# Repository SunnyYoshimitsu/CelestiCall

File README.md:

# CelestiCall
 An attempt at making a somewhat modern smartphone with many functions. 

CelestiCall is a phone with a somewhat outdated concept that I've come up with for the Summer of 2024. The purpose of the phone? to allow me to learn and get experience on many computer subjects all at once. 
And what are those "experience" and "subjects" I'm talking about? They're power system design, FPGA design, 3D printing, communication, Linux, web design and many more.

Let me tell about what I see this phone will have as I want this to be unique and with quite a large amount of personal touch up. 
1) This phone will be running on an FPGA, specifically Zynq FPGAs. This is because I want to learn about how to create a whole SoC from scratch (with a hardcore A9 of course), as this will teach me about the SoC design and more. 
2) It will serve as both a phone and as a portable small Linux computer with HDMI. This is one reason why I said the concept is a little outdated as many modern phone can just screen share to TV and call it a day. However since my phone won't be in any of the TV's ecosystem, I will "cheat" and have it "screen-share" via HDMI. My inspiration is the ChromeBit and the Motorola Atrix HD.
3) I also will have a web "program" very much similar to what ChromeOS offer but obviously way more bootleg as it will be made by one person. This is a way that I will be able to artificially extend the power of the little device by having many computing heavy problems or storage be on the cloud. 

Here I'll go into a personal requirement for what I think the smartphone should be and have. I'll describe the software and the hardware along with the type of apps I would like to have running on it.

Requirement: 
* Interaction : All modern smartphone have touchscreens and really that's one of the reason that started the smartphone trend. I might add some physical buttons but that's up for considerations.
* 
* Communication : A phone is not a phone if one can't call from it. I'll make the phone being able to use 4G and possibly 5G as 3G and below at least in the US is defunct. Also this hopefully will allow the phone to access the internet.
* 
* Usage Time : The target is the battery lasting up to a whole day on a single charge on heavy use. I will go into what "heavy use" entails later.
* 
* Operating System : Linux is a must and also more like an existing distro. If possible and if the system is powerful enough I might use Android(possibly 2.0) since I don't have the manpower to make my own softwares.
There wil be this much requirement for now, it might be changed later.

Hardware: 
Physical dimesion: Similar to that of Iphone I or the various Window phones. 
                   Small and comact as to be able to reach from bottom of the screen to the top. 
                   
Computer Hardware: Runs off dual Cortex A9 on an FPGA and hopefully give up to 2GB of RAM. 
                   ARM A9 is a relative strong chips that could run many lightweight Linux distro without much problem. 

Software: 
Onboard-based: Android 2.0 would be preferrable
               It's a widely used distro with a lot of available softwares
               
Web-based: Something like a personal/homebrew Google Drive and the ability to use a home server as extra computing extension and a NAS as online hard-drive. 
           This would allow the device to be more than it can be

Here's the architecture of the SoC would look like: 
Note: if there's an asterisk, it means that that specific part will be custom. 

Roadmap

*Software to make calls, use WiFi, send/receive SMS, GPS and take photos in any GNU/linux:
    Estimated Time: ~5 months
    
    With hardware:
                  A7670G with ESP32: https://github.com/Xinyuan-LilyGO/LilyGO-T-A76XX
                  Quectel: https://www.aliexpress.us/item/3256806123411827.html?src=google&gatewayAdapt=glo2usa
    With software: 
                  Android 5 for Zedboard: https://github.com/noritsuna/zedroid_system_core?tab=readme-ov-file
                  Android 4 for Pynq Z2: https://xilinx-wiki.atlassian.net/wiki/spaces/A/pages/18842042/Android+4.2.2+On+Zynq+Getting+Started+Guide
                  AT commands for the GPRS 
                  Arduino C codes for ESP32 wiFi and BLE

*Touchscreen, buttons and audio I/Os:
    Estimated Time: ~2 months

    Note: as of 5/23/2024, I'm still deciding whether to pursue a phone with large or small screens. They could be as large as a modern Iphone Pro Max with screen going up to near 7inch or older phones with screen as small as 3-inch diagnally. 

    With hardware: 
                 Small 3.1 in screen: https://tailorpixels.com/product/3-1-inch-ips-tft-high-resolution-mipi/
                 Medium sized 5 in screen: https://tailorpixels.com/product/5-inch-tn-tft-lcd-rgb-800x480-landscape/
                 Large sized 7 in screen: https://tailorpixels.com/product/7-inch-tn-tft-lcd-rgb-800x480/
    With software: 
                 -For starter: a framebuffer in RAM
                 -End goal: running on a custom GPU (HyperNova)

The above two steps will be prototyped via COTS development boards and easy to use breadboard.

*Make a prototype PCB with components:

    Estimated Time: ~2 months 
    Estimated cost: ~$400

    1) Start with a simple FPGA board
    2) Add peripherals like the WiFI, GPRS and camera
    3) Add touchscreen and physical input (buttons)

 *Design and manufacture outer shell:
    Estimated Time: ~2 months
    Estimated cost: ~$50

    Design concept: The shell of the phone will be somewhat similar looking to any modern smartphone, however it will be thicker than the norm. This is to be able to accomodate at least two full size USB and HDMI ports along with possibly 2 PMODs interface. 

    With hardware: 
                 Bambu Lab 3D printer
    With software: 
                 Krita for concept art
                 Solidwork for the end product

 *End Step: 
    This step will involve the creation of the "bootleg Google Drive" that I've detailed in the beginning along with making a case for the phone.
     
Rough Project Timeline/Plans:

To do list/learn/plan(6/17):

Start making prototypes of the GPU and the Audio mixer
Then integrate them to a HDMI output

GPU: Learn about "CUDA" cores, make a RGB framebuffer of 800 x 600 size for the touchscreen output. Make variable screen resolution for HDMI out. 
Audio: extend upon school filter projects and DMA sound replay. 
       If too complicated, then make a simple PCM passthrough and FIFO for sound replay from memory. 

Integrate both GPU and Audio though the HyperNova top module to output to HDMI, display and audio jack. Add controls to allow versatile displaying. 
Possibly add possible VGA output for second display via the PMOD (max 64 colors only). 

I know this sounds ambitious as going to the moon by oneself. HOWEVER, with the way technology is evolving, I believe it's possible....Please let a student dream.....

Email: huynguyenwork123@gmail.com

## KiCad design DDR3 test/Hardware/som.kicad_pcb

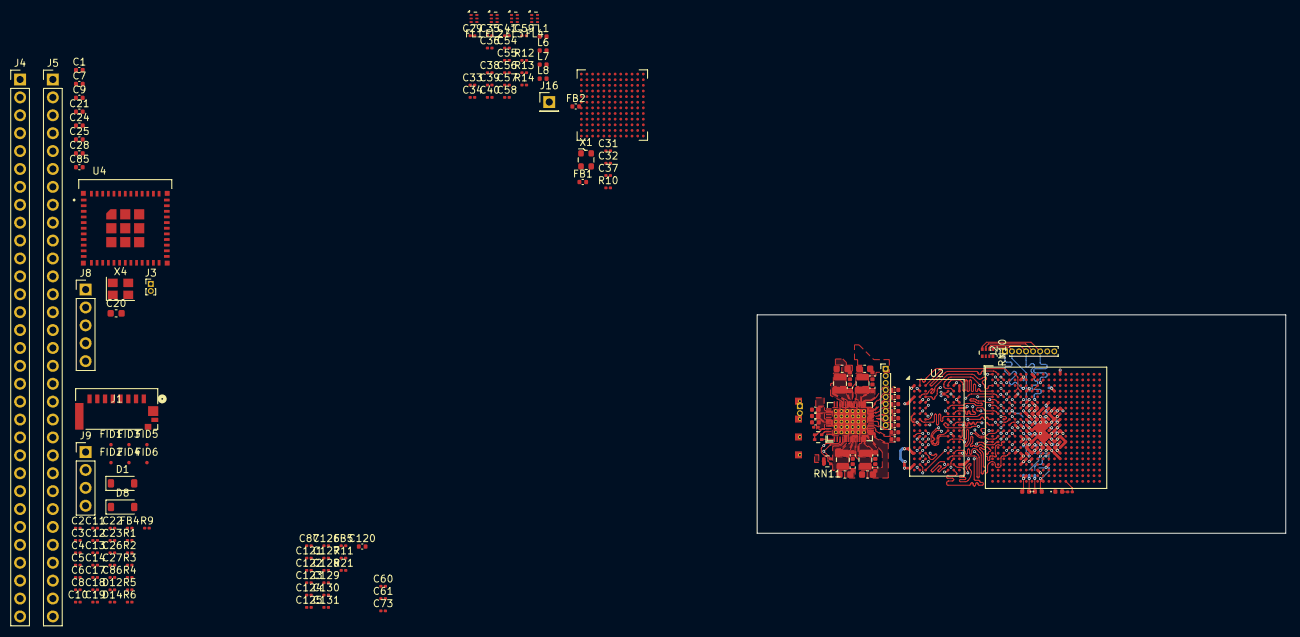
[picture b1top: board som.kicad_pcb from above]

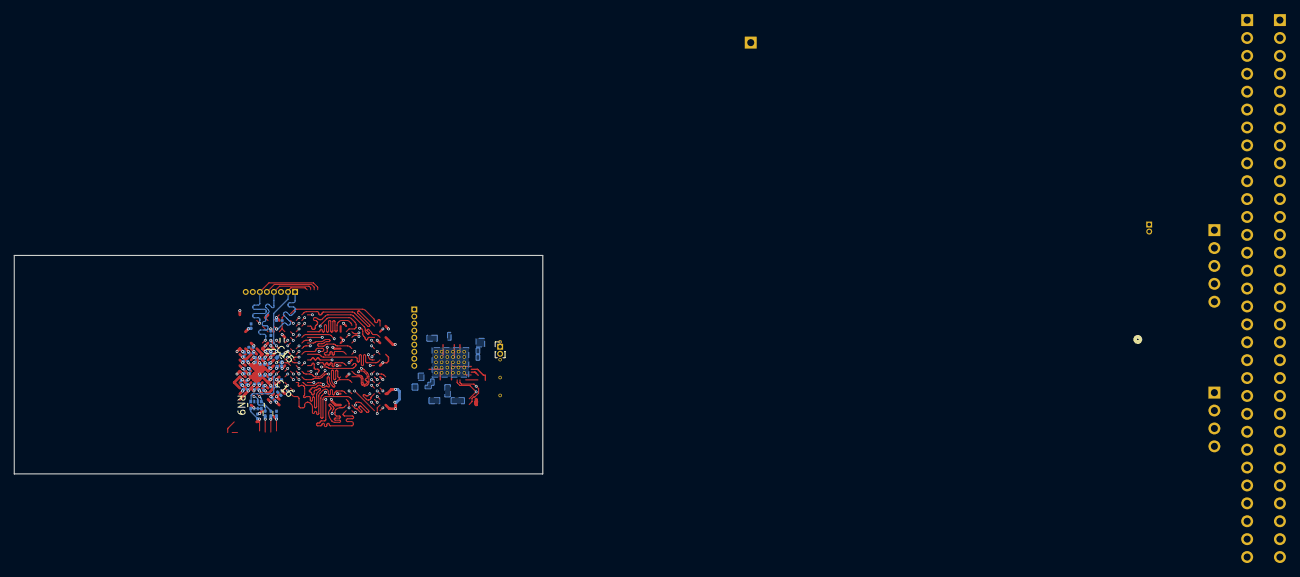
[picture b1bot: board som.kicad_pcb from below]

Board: 6 copper layers, 75.0 x 31.0 mm, 186 parts (37 on the bottom side), 206 nets.

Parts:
C1, C7, C9, C15, C24, C25, C28: 10uF; C_0402_1005Metric
C2, C3, C4, C5, C6, C8, C10, C11, C12, C13, C14, C16, C17, C18, C19, C23, C26, C27, C29, C31, C32, C33, C34, C35, C36, C38, C39, C40, C41, C54, C55, C57, C58, C59, C60, C61, C73: 0.1uF; C_0201_0603Metric
C20, C97, C100, C105, C107: 22uF; C_0603_1608Metric
C21, C85, C96, C98, C99, C101, C102, C103, C104, C106, C108, C109, C110, C111, C112, C113, C114, C115, C116, C117, C119, C120: 4u7F; C_0402_1005Metric
C22, C42, C43, C44, C45, C46, C47, C48, C49, C50, C51, C52, C62, C63, C64, C65, C66, C67, C68, C69, C70, C72, C86, C87, C88, C89, C90, C91, C92, C93, C118, C121, C122, C123, C124, C125, C126, C127, C128, C129, C130, C131: 100nF; C_0201_0603Metric
C37, C56: 18pF; C_0201_0603Metric
C53, C94: 100nF; C_0201_0603Metric_WideGap
C71: 4u7F; C_0201_0603Metric_WideGap
D1, D8: SUPK24; D_SOD-123
D2: DONE_LED; LED_0402_1005Metric
D3: INIT_LED; LED_0402_1005Metric
D7: LED3; LED_0402_1005Metric
D12, D14: TVS; R_0201_0603Metric
FB1, FB2: FerriteBead_Small; C_0402_1005Metric
FB3, FB4, FB5: 120Ω; L_0201_0603Metric
FID1, FID2, FID3, FID4, FID5, FID6: Fiducial; Fiducial_0.5mm_Mask1mm
FL1, FL2, FL3, FL4: 0850BM14E0016; Balun_Johanson_1.6x0.8mm
J1: TF; CONN12_47309-2651_MOL
J2: Conn_Debug; PinHeader_1x08_P1.00mm_Vertical
J3: Conn_MP; PinHeader_1x02_P1.00mm_Vertical
J4, J5: Conn_PB; PinHeader_1x31_P2.54mm_Vertical
J6: Conn_PWR; PinHeader_1x09_P1.00mm_Vertical
J7: Conn_IIC; PinHeader_1x02_P1.00mm_Vertical
J8: Conn_01x05_Pin; PinHeader_1x05_P2.54mm_Vertical
J9: Conn_01x04_Pin; PinHeader_1x04_P2.54mm_Vertical
J16: Conn_01x01; PinHeader_1x01_P2.54mm_Vertical
L1, L6, L7, L8: L; L_0402_1005Metric
L2, L3, L4, L5: 1uH; L_0806_2016Metric
R1, R4, R5: 80Ω; R_0201_0603Metric
R2: 4.7K; R_0201_0603Metric
R3: 4K7Ω; R_0201_0603Metric
R6: 240Ω; R_0201_0603Metric
R7, R8, R20: R; R_0201_0603Metric
R9, R21: 22Ω; R_0201_0603Metric
R10, R13: 0R; R_0201_0603Metric
R11: 40Ω; R_0201_0603Metric
R12: 14.3K; R_0201_0603Metric
R14: N/A; R_0201_0603Metric
RN9, RN10: 4K7Ω; R_Array_Convex_4x0402
RN11: 4K7Ω; R_Array_Convex_2x0402
RN12: 10KΩ; R_Array_Convex_2x0402
TP1: PMIC_PROG; TP_4pin_2.54mm
U1: XC7Z010CLG400; Xilinx_CLG400_NoPaste_JLC_Package_Delay
U2: DDR3; Micron_FBGA-96_7.5x13.5mm_Layout9x16_P0.8mm
U3: AD9361; bga-100_10_10_1p32_0p8
U4: ESP32-C6-MINI-1U-N4; XCVR_ESP32-C6-MINI-1U-N4
U7: STPMIC1; ST-WFQFN-44L_5x6mm_P0.4mm_ThermalVias
X1: SiT1602B; Oscillator_SMD_ECS_2520MV-xxx-xx-4Pin_2.5x2.0mm
X4: 33.3MHz; Crystal_SMD_3225-4Pin_3.2x2.5mm

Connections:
+1V0: C42.1, C43.1, C44.1, C45.1, C46.1, C47.1, C48.1, C49.1, C50.1, C51.1, C52.1, C53.1, C97.1, C98.1, L2.2, U1.G7 (VCCPINT[6]), U1.G11 (VCCBRAM[2]), U1.G13 (VCCINT[9]), U1.H10 (VCCBRAM[2]), U1.H12 (VCCINT[9]), U1.J7 (VCCPINT[6]), U1.J13 (VCCINT[9]), U1.K12 (VCCINT[9]), U1.L7 (VCCPINT[6]), U1.L13 (VCCINT[9]), U1.M12 (VCCINT[9]), U1.N7 (VCCPINT[6]), U1.N13 (VCCINT[9]), U1.P8 (VCCPINT[6]), U1.P12 (VCCINT[9]), U1.R7 (VCCPINT[6]), U1.R13 (VCCINT[9]), U7.5 (VOUT1)
+1V8: C29.1, C60.1, C61.1, C62.1, C63.1, C64.1, C65.1, C66.1, C67.1, C68.1, C69.1, C70.1, C73.1, C105.1, C106.1, FB3.2, J6.2, L4.2, U1.C19 (VCCO_35[6]), U1.F8 (VCCPAUX[5]), U1.F11 (VCCBATT_0), U1.F18 (VCCO_35[6]), U1.G9 (VCCPAUX[5]), U1.H8 (VCCPAUX[5]), U1.H14 (VCCO_35[6]), U1.J9 (VCCADC_0), U1.J11 (VCCAUX[6]), U1.J17 (VCCO_35[6]), U1.K8 (VCCPAUX[5]), U1.K20 (VCCO_35[6]), U1.L11 (VCCAUX[6]), U1.M8 (VCCPAUX[5]), U1.M16 (VCCO_35[6]), U1.N9 (VCCAUX[6]), U1.N11 (VCCAUX[6]), U1.P10 (VCCAUX[6]), U1.R9 (VCCAUX[6]), U7.31 (VOUT3), X1.4 (VDD)
+3.3VA: C116.1, J4.19, RN11.3 (R2.2), RN11.4 (R1.2), RN12.3 (R2.2), RN12.4 (R1.2), U7.39 (LDO4OUT), U7.42 (VIO)
+3V3: C20.1, C21.1, C22.1, C87.1, C88.1, C89.1, C90.1, C91.1, C92.1, C93.1, C94.1, C107.1, C108.1, C127.1, C128.1, C129.1, C130.1, C131.1, D2.2 (A), D3.2 (A), FB4.2, FB5.2, J1.4 (VDD), J2.8, J3.1, J5.2, J5.20, J6.1, L5.2, R3.1, RN9.1 (R1.1), RN9.2 (R2.1), RN9.3 (R3.1), RN9.4 (R4.1), RN10.5 (R4.2), RN10.6 (R3.2), RN10.7 (R2.2), RN10.8 (R1.2), U1.A6 (PS_MIO5_500), U1.A13 (VCCO_MIO1_501[4]), U1.B6 (VCCO_MIO0_500[2]), U1.B7 (PS_MIO4_500), U1.B16 (VCCO_MIO1_501[4]), U1.D7 (VCCO_MIO0_500[2]), U1.D12 (VCCO_MIO1_501[4]), U1.E15 (VCCO_MIO1_501[4]), U1.K6 (VCCO_0), U1.M6 (CFGBVS_0), U1.N6 (RSVDVCC3), U1.R6 (RSVDVCC2), U1.T6 (RSVDVCC1), U1.T8 (VCCO_13[4]), U1.U11 (VCCO_13[4]), U1.W7 (VCCO_13[4]), U1.Y10 (VCCO_13[4]), U4.3 (3V3), U7.27 (VOUT4)
+5V: C96.1, C99.1, C102.1, C104.1, C109.1, C112.1, C119.1, D1.1 (K), D8.1 (K), D12.1 (A1), D14.1 (A1), J4.9, J4.10, J6.5, J6.8, TP1.3, U7.8 (BUCK1IN), U7.12 (BUCK2IN), U7.19 (LDO25IN), U7.22 (LDO16IN), U7.24 (BUCK4IN), U7.28 (BUCK3IN), U7.36 (VIN)
/BUCK1OUT: L2.1, U7.7 (VLX1)
/BUCK2OUT: L3.1, U7.11 (VLX2)
/BUCK3OUT: L4.1, U7.29 (VLX3)
/BUCK4OUT: L5.1, U7.25 (VLX4)
/DDR_A0: U1.N2 (PS_DDR_A0_502), U2.N3 (A0)
/DDR_A1: U1.K2 (PS_DDR_A1_502), U2.P7 (A1)
/DDR_A2: U1.M3 (PS_DDR_A2_502), U2.P3 (A2)
/DDR_A3: U1.K3 (PS_DDR_A3_502), U2.N2 (A3)
/DDR_A4: U1.M4 (PS_DDR_A4_502), U2.P8 (A4)
/DDR_A5: U1.L1 (PS_DDR_A5_502), U2.P2 (A5)
/DDR_A6: U1.L4 (PS_DDR_A6_502), U2.R8 (A6)
/DDR_A7: U1.K4 (PS_DDR_A7_502), U2.R2 (A7)
/DDR_A8: U1.K1 (PS_DDR_A8_502), U2.T8 (A8)
/DDR_A9: U1.J4 (PS_DDR_A9_502), U2.R3 (A9)
/DDR_A10: U1.F5 (PS_DDR_A10_502), U2.L7 (A10/AP)
/DDR_A11: U1.G4 (PS_DDR_A11_502), U2.R7 (A11)
/DDR_A12: U1.E4 (PS_DDR_A12_502), U2.N7 (A12/~BC)
/DDR_A13: U1.D4 (PS_DDR_A13_502), U2.T3 (A13)
/DDR_A14: U1.F4 (PS_DDR_A14_502), U2.T7 (A14)
/DDR_BA0: U1.L5 (PS_DDR_BA0_502), U2.M2 (BA0)
/DDR_BA1: U1.R4 (PS_DDR_BA1_502), U2.N8 (BA1)
/DDR_BA2: U1.J5 (PS_DDR_BA2_502), U2.M3 (BA2)
/DDR_CKE: U1.N3 (PS_DDR_CKE_502), U2.K9 (CKE)
/DDR_DQ0: U1.E2 (PS_DDR_DQ8_502), U2.E3 (DQ0)
/DDR_DQ1: U1.E3 (PS_DDR_DQ9_502), U2.F7 (DQ1)
/DDR_DQ2: U1.H2 (PS_DDR_DQ13_502), U2.F2 (DQ2)
/DDR_DQ3: U1.G3 (PS_DDR_DQ10_502), U2.F8 (DQ3)
/DDR_DQ4: U1.J1 (PS_DDR_DQ15_502), U2.H3 (DQ4)
/DDR_DQ5: U1.J3 (PS_DDR_DQ12_502), U2.H8 (DQ5)
/DDR_DQ6: U1.H1 (PS_DDR_DQ14_502), U2.G2 (DQ6)
/DDR_DQ7: U1.H3 (PS_DDR_DQ11_502), U2.H7 (DQ7)
/DDR_DQ8: U1.C3 (PS_DDR_DQ0_502), U2.D7 (DQ8)
/DDR_DQ9: U1.B3 (PS_DDR_DQ1_502), U2.C3 (DQ9)
/DDR_DQ10: U1.E1 (PS_DDR_DQ7_502), U2.C8 (DQ10)
/DDR_DQ11: U1.C1 (PS_DDR_DQ6_502), U2.C2 (DQ11)
/DDR_DQ12: U1.D1 (PS_DDR_DQ5_502), U2.A7 (DQ12)
/DDR_DQ13: U1.A4 (PS_DDR_DQ3_502), U2.A2 (DQ13)
/DDR_DQ14: U1.D3 (PS_DDR_DQ4_502), U2.B8 (DQ14)
/DDR_DQ15: U1.A2 (PS_DDR_DQ2_502), U2.A3 (DQ15)
/DDR_DQM0: U1.F1 (PS_DDR_DM1_502), U2.E7 (LDM)
/DDR_DQM1: U1.A1 (PS_DDR_DM0_502), U2.D3 (UDM)
/DDR_DQS0+: U1.G2 (PS_DDR_DQS_P1_502), U2.F3 (LDQS)
/DDR_DQS0-: U1.F2 (PS_DDR_DQS_N1_502), U2.G3 (~LDQS)
/DDR_DQS1+: U1.C2 (PS_DDR_DQS_P0_502), U2.C7 (UDQS)
/DDR_DQS1-: U1.B2 (PS_DDR_DQS_N0_502), U2.B7 (~UDQS)
/DDR_ODT: U1.N5 (PS_DDR_ODT_502), U2.K1 (ODT)
/DDR_VRN: R4.1, U1.G5 (PS_DDR_VRN_502)
/DDR_VRP: R5.1, U1.H5 (PS_DDR_VRP_502)
/DDR_nCAS: U1.P5 (PS_DDR_CAS_B_502), U2.K3 (~CAS)
/DDR_nCS: U1.N1 (PS_DDR_CS_B_502), U2.L2 (~CS)
/DDR_nRAS: U1.P4 (PS_DDR_RAS_B_502), U2.J3 (~RAS)
/DDR_nWE: U1.M5 (PS_DDR_WE_B_502), U2.L3 (~WE)
/DONE_: D2.1 (K), R7.2
/EXT_SYNC: J16.1, R14.1
/INIT_: D3.1 (K), R8.2
/LED3_: D7.2 (A), R20.2
/PMIC_INTLDO: C117.1, C118.1, U7.40 (INTLDO)
/PS_CLK_: R9.1, X4.3 (OUT)
/SD0_CK_: R11.1, U1.D14 (PS_MIO40_501)
/TRANS_CMOS_FB_CLK: U1.K18 (IO_L12N_T1_MRCC_35), U3.F10 (FB_CLK+)
/TRANS_CMOS_RX_D0: U1.E17 (IO_L3P_T0_DQS_AD1P_35), U3.K11 (P1_D0/RX_D0-)
/TRANS_CMOS_RX_D1: U1.F16 (IO_L6P_T0_35), U3.J12 (P1_D1/RX_D0+)
/TRANS_CMOS_RX_D2: U1.J20 (IO_L17P_T2_AD5P_35), U3.K10 (P1_D2/RX_D1-)
/TRANS_CMOS_RX_D3: U1.F17 (IO_L6N_T0_VREF_35), U3.J11 (P1_D3/RX_D1+)
/TRANS_CMOS_RX_D4: U1.F20 (IO_L15N_T2_DQS_AD12N_35), U3.K9 (P1_D4/RX_D2-)
/TRANS_CMOS_RX_D5: U1.G15 (IO_L19N_T3_VREF_35), U3.J10 (P1_D5/RX_D2+)
/TRANS_CMOS_RX_D6: U1.G19 (IO_L18P_T2_AD13P_35), U3.K8 (P1_D6/RX_D3-)
/TRANS_CMOS_RX_D7: U1.G17 (IO_L16P_T2_35), U3.J9 (P1_D7/RX_D3+)
/TRANS_CMOS_RX_D8: U1.E18 (IO_L5P_T0_AD9P_35), U3.K7 (P1_D8/RX_D4-)
/TRANS_CMOS_RX_D9: U1.G18 (IO_L16N_T2_35), U3.J8 (P1_D9/RX_D4+)
/TRANS_CMOS_RX_D10: U1.E19 (IO_L5N_T0_AD9N_35), U3.J7 (P1_D10/RX_D5-)
/TRANS_CMOS_RX_D11: U1.H18 (IO_L14N_T2_AD4N_SRCC_35), U3.H8 (P1_D11/RX_D5+)
/TRANS_CMOS_RX_FRAME: U1.H17 (IO_L13N_T2_MRCC_35), U3.G8 (RX_FRAME+)
/TRANS_CMOS_TX_D0: U1.M18 (IO_L8N_T1_AD10N_35), U3.E12 (P0_D0/TX_D0-)
/TRANS_CMOS_TX_D1: U1.L17 (IO_L11N_T1_SRCC_35), U3.D11 (P0_D1/TX_D0+)
/TRANS_CMOS_TX_D2: U1.M19 (IO_L7P_T1_AD2P_35), U3.E11 (P0_D2/TX_D1-)
/TRANS_CMOS_TX_D3: U1.M15 (IO_L23N_T3_35), U3.D10 (P0_D3/TX_D1+)
/TRANS_CMOS_TX_D4: U1.K16 (IO_L24P_T3_AD15P_35), U3.E10 (P0_D4/TX_D2-)
/TRANS_CMOS_TX_D5: U1.M17 (IO_L8P_T1_AD10P_35), U3.D9 (P0_D5/TX_D2+)
/TRANS_CMOS_TX_D6: U1.J16 (IO_L24N_T3_AD15N_35), U3.E9 (P0_D6/TX_D3-)
/TRANS_CMOS_TX_D7: U1.N16 (IO_L21N_T3_DQS_AD14N_35), U3.D8 (P0_D7/TX_D3+)
/TRANS_CMOS_TX_D8: U1.L16 (IO_L11P_T1_SRCC_35), U3.E8 (P0_D8/TX_D4-)
/TRANS_CMOS_TX_D9: U1.M14 (IO_L23P_T3_35), U3.D7 (P0_D9/TX_D4+)
/TRANS_CMOS_TX_D10: U1.H15 (IO_L19P_T3_35), U3.F8 (P0_D10/TX_D5-)
/TRANS_CMOS_TX_D11: U1.K19 (IO_L10P_T1_AD11P_35), U3.E7 (P0_D11/TX_D5+)
/TRANS_CMOS_TX_FRAME: U1.J19 (IO_L10N_T1_AD11N_35), U3.G9 (TX_FRAME+)
/TRANS_CTRL_IN0: U1.L14 (IO_L22P_T3_AD7P_35), U3.C5 (CTRL_IN0)
/TRANS_CTRL_IN1: U1.L15 (IO_L22N_T3_AD7N_35), U3.C6 (CTRL_IN1)
/TRANS_CTRL_IN2: U1.J15 (IO_25_35), U3.D6 (CTRL_IN2)
/TRANS_CTRL_IN3: U1.K14 (IO_L20P_T3_AD6P_35), U3.D5 (CTRL_IN3)
/TRANS_CTRL_OUT0: U1.B20 (IO_L1N_T0_AD0N_35), U3.D4 (CTRL_OUT0)
/TRANS_CTRL_OUT1: U1.A20 (IO_L2N_T0_AD8N_35), U3.E4 (CTRL_OUT1)
/TRANS_CTRL_OUT2: U1.J14 (IO_L20N_T3_AD6N_35), U3.E5 (CTRL_OUT2)
/TRANS_CTRL_OUT3: U1.C20 (IO_L1P_T0_AD0P_35), U3.E6 (CTRL_OUT3)
/TRANS_CTRL_OUT4: U1.G20 (IO_L18N_T2_AD13N_35), U3.F6 (CTRL_OUT4)
/TRANS_CTRL_OUT5: U1.N15 (IO_L21P_T3_DQS_AD14P_35), U3.F5 (CTRL_OUT5)
/TRANS_CTRL_OUT6: U1.L20 (IO_L9N_T1_DQS_AD3N_35), U3.F4 (CTRL_OUT6)
/TRANS_CTRL_OUT7: U1.D19 (IO_L4P_T0_35), U3.G4 (CTRL_OUT7)
/TRANS_ENABLE: U1.D18 (IO_L3N_T0_DQS_AD1N_35), U3.G6 (ENABLE)
/TRANS_ENAGC: U1.J18 (IO_L14P_T2_AD4P_SRCC_35), U3.G5 (EN_AGC)
/TRANS_MRCC_CLKOUT: U1.H16 (IO_L13P_T2_MRCC_35), U3.J6 (CLK_OUT)
/TRANS_MRCC_DATA_CLK: U1.K17 (IO_L12P_T1_MRCC_35), U3.G11 (DATA_CLK+)
/TRANS_OSC_N: C37.1, X1.3 (OUT)
/TRANS_RBIAS: R12.1, U3.L4 (RBIAS)
/TRANS_RST: U1.B14 (PS_MIO47_501), U3.K5 (~RESET)
/TRANS_RXRF0_N: C39.1, FL3.3 (RF_N)
/TRANS_RXRF0_P: C38.1, FL3.4 (RF_P)
/TRANS_RXRF1_N: C54.1, FL4.3 (RF_N)
/TRANS_RXRF1_P: C41.1, FL4.4 (RF_P)
/TRANS_SPI_CLK: U1.A16 (PS_MIO24_501), U3.J5 (SPI_CLK)
/TRANS_SPI_MISO: U1.D11 (PS_MIO23_501), U3.L6 (SPI_MISO)
/TRANS_SPI_MOSI: U1.B17 (PS_MIO22_501), U3.J4 (SPI_MOSI)
/TRANS_SPI_SS: U1.F15 (PS_MIO25_501), U3.K6 (SPI_~EN)
/TRANS_SYNC: R13.1, U1.H20 (IO_L17N_T2_AD5N_35)
/TRANS_TXNRX: U1.D20 (IO_L4N_T0_35), U3.H4 (TX~RX)
/TRANS_TXRF0_N: C33.1, FL1.4 (RF_P)
/TRANS_TXRF0_P: C34.1, FL1.3 (RF_N)
/TRANS_TXRF1_N: C36.1, FL2.4 (RF_P)
/TRANS_TXRF1_P: C35.1, FL2.3 (RF_N)
/VCC_PLL: C71.1, C72.1, FB3.1, U1.G8 (VCCPLL)
/VCC_PL_CLK: C120.1, C121.1, FB5.1
/VCC_PS_CLK: C85.1, C86.1, FB4.1, X4.1 (EN), X4.4 (Vdd)
/VREF_DDR1: C18.1, C23.1, C24.1, U1.H6 (PS_DDR_VREF0_502), U1.P6 (PS_DDR_VREF1_502)
/VREF_DDR2: C26.1, U2.M8 (VREFCA)
/VREF_DDR3: C28.1, U2.H1 (VREFDQ)
DDR_CK+: R1.1, U1.L2 (PS_DDR_CKP_502), U2.J7 (CK)
DDR_CK-: R1.2, U1.M2 (PS_DDR_CKN_502), U2.K7 (~CK)
DDR_nRST: R2.1, U1.B4 (PS_DDR_DRST_B_502), U2.T2 (~RESET)
DONE: R7.1, RN9.6 (R3.2), U1.R11 (DONE_0)
GND: C1.2, C2.2, C3.2, C4.2, C5.2, C6.2, C7.2, C8.2, C9.2, C10.2, C11.2, C12.2, C13.2, C14.2, C15.2, C16.2, C17.2, C18.2, C19.2, C20.2, C21.2, C22.2, C23.2, C24.2, C25.2, C26.2, C27.2, C28.2, C29.2, C31.1, C32.1, C42.2, C43.2, C44.2, C45.2, C46.2, C47.2, C48.2, C49.2, C50.2, C51.2, C52.2, C53.2, C56.1, C57.1, C58.1, C59.1, C60.2, C61.2, C62.2, C63.2, C64.2, C65.2, C66.2, C67.2, C68.2, C69.2, C70.2, C71.2, C72.2, C73.2, C85.2, C86.2, C87.2, C88.2, C89.2, C90.2, C91.2, C92.2, C93.2, C94.2, C96.2, C97.2, C98.2, C99.2, C100.2, C101.2, C102.2, C103.2, C104.2, C105.2, C106.2, C107.2, C108.2, C109.2, C110.2, C111.2, C112.2, C113.2, C114.2, C115.2, C116.2, C117.2, C118.2, C119.2, C120.2, C121.2, C122.2, C123.2, C124.2, C125.2, C126.2, C127.2, C128.2, C129.2, C130.2, C131.2, D7.1 (K), D12.2 (A2), D14.2 (A2), FL1.5 (GND), FL1.6 (GND), FL2.5 (GND), FL2.6 (GND), FL3.5 (GND), FL3.6 (GND), FL4.5 (GND), FL4.6 (GND), J1.6 (VSS), J1.G1, J1.G2, J1.G3, J1.G4, J2.7, J3.2, J4.11, J4.12, J4.27, J4.30, J4.31, J5.18, J5.19, J6.3, J9.4, R2.2, R5.2, R6.1, R12.2, TP1.4, U1.A5 (PS_MIO6_500), U1.A8 (GND[59]), U1.A18 (GND[59]), U1.B1 (GND[59]), U1.B8 (PS_MIO2_500), U1.B11 (GND[59]), U1.C4 (GND[59]), U1.C9 (GND[59]), U1.C14 (GND[59]), U1.D5 (PS_MIO8_500), U1.D6 (PS_MIO3_500), U1.D8 (PS_MIO7_500), U1.D17 (GND[59]), U1.E10 (GND[59]), U1.E20 (GND[59]), U1.F3 (GND[59]), U1.F7 (GND[59]), U1.G10 (GND[59]), U1.G12 (GND[59]), U1.G16 (GND[59]), U1.H7 (GND[59]), U1.H9 (GND[59]), U1.H11 (GND[59]), U1.H13 (GND[59]), U1.H19 (GND[59]), U1.J2 (GND[59]), U1.J8 (GND[59]), U1.J10 (GNDADC_0), U1.J12 (GND[59]), U1.K5 (GND[59]), U1.K7 (GND[59]), U1.K9 (VP_0), U1.K10 (VREFN_0), U1.K11 (GND[59]), U1.K13 (GND[59]), U1.K15 (GND[59]), U1.L8 (GND[59]), U1.L9 (VREFP_0), U1.L10 (VN_0), U1.L12 (GND[59]), U1.L18 (GND[59]), U1.M1 (GND[59]), U1.M7 (GND[59]), U1.M9 (DXP_0), U1.M10 (DXN_0), U1.M11 (GND[59]), U1.M13 (GND[59]), U1.N4 (GND[59]), U1.N8 (GND[59]), U1.N10 (GND[59]), U1.N12 (GND[59]), U1.N14 (GND[59]), U1.P7 (GND[59]), U1.P9 (GND[59]), U1.P11 (GND[59]), U1.P13 (GND[59]), U1.P17 (GND[59]), U1.R8 (GND[59]), U1.R12 (GND[59]), U1.R20 (GND[59]), U1.T3 (GND[59]), U1.T7 (GND[59]), U1.T13 (GND[59]), U1.U6 (GND[59]), U1.U16 (GND[59]), U1.V9 (GND[59]), U1.V19 (GND[59]), U1.W2 (GND[59]), U1.W12 (GND[59]), U1.Y5 (GND[59]), U1.Y15 (GND[59]), U2.A9 (VSS), U2.B1 (VSSQ), U2.B3 (VSS), U2.B9 (VSSQ), U2.D1 (VSSQ), U2.D8 (VSSQ), U2.E1 (VSS), U2.E2 (VSSQ), U2.E8 (VSSQ), U2.F9 (VSSQ), U2.G1 (VSSQ), U2.G8 (VSS), U2.G9 (VSSQ), U2.J2 (VSS), U2.J8 (VSS), U2.M1 (VSS), U2.M9 (VSS), U2.P1 (VSS), U2.P9 (VSS), U2.T1 (VSS), U2.T9 (VSS), U3.C1 (RX2C-), U3.D1 (RX2C+), U3.E1 (RX2B+), U3.F1 (RX2B-), U3.G7 (RX_FRAME-), U3.G10 (FB_CLK-), U3.H1 (RX1B+), U3.H9 (TX_FRAME-), U3.J1 (RX1B-), U3.K1 (RX1C+), U3.L1 (RX1C-), U4.1 (GND1), U4.2 (GND1__1), U4.11 (GND1__2), U4.14 (GND1__3), U4.36 (GND1__4), U4.37 (GND1__5), U4.38 (GND1__6), U4.39 (GND1__7), U4.40 (GND1__8), U4.41 (GND1__9), U4.42 (GND1__10), U4.43 (GND1__11), U4.44 (GND1__12), U4.45 (GND1__13), U4.46 (GND1__14), U4.47 (GND2), U4.48 (GND2__1), U4.49_1 (GND2__2), U4.49_2 (GND2__3), U4.49_3 (GND2__4), U4.49_4 (GND2__5), U4.49_5 (GND2__6), U4.49_6 (GND2__7), U4.49_7 (GND2__8), U4.49_8 (GND2__9), U4.49_9 (GND2__10), U4.50 (GND2__11), U4.51 (GND2__12), U4.52 (GND2__13), U4.53 (GND2__14), U7.6 (PGND1), U7.10 (PGND2), U7.15 (GNDLDO), U7.26 (PGND4)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
INIT: R8.1, RN9.5 (R4.2), U1.R10 (INIT_B_0)
JTAG_TCK: J2.4, RN10.2 (R2.1), U1.F9 (TCK_0), U4.9 (IO4)
JTAG_TDI: J2.2, RN10.1 (R1.1), U1.G6 (TDI_0), U4.5 (IO2)
JTAG_TDO: J2.3, U1.F6 (TDO_0), U4.6 (IO3)
JTAG_TMS: J2.5, RN10.3 (R3.1), U1.J6 (TMS_0), U4.10 (IO5)
LDO2: C113.1, J6.9, U7.18 (LDO2OUT)
LDO5: C114.1, J6.7, U7.20 (LDO5OUT)
LDO6: C111.1, J6.6, U7.21 (LDO6OUT)
LED3: R20.1, U1.Y14 (IO_L8N_T1_34)
MB_SCL: J7.2, RN11.2 (R2.1), TP1.2, U7.4 (SCL)
MB_SDA: J7.1, RN11.1 (R1.1), TP1.1, U7.3 (SDA)
N20+: J4.1, U1.N20 (IO_L14P_T2_SRCC_34)
unnamed: D1.2 (A), J5.1
unnamed: D8.2 (A), J8.5
unnamed: R6.2, U2.L8 (ZQ)
unnamed: C38.2, U3.M1 (RX1A+)
unnamed: C39.2, U3.M2 (RX1A-)
unnamed: C41.2, U3.A2 (RX2A+)
unnamed: C54.2, U3.A1 (RX2A-)
unnamed: C55.2, U3.G1 (RX_EXT_LO_IN)
unnamed: R13.2, R14.2, U3.H5 (SYNC_IN)
unnamed: C34.2, L1.2, U3.M7 (TX1A+)
unnamed: C33.2, L6.2, U3.M8 (TX1A-)
unnamed: C31.2, C32.2, FB1.2, L1.1, L6.1, U3.M9 (TX1B+), U3.M10 (TX1B-)
unnamed: C35.2, L7.2, U3.A8 (TX2A+)
unnamed: C36.2, L8.2, U3.A7 (TX2A-)
unnamed: C57.2, C58.2, C59.2, FB2.2, L7.1, L8.1, U3.A9 (TX2B-), U3.A10 (TX2B+)
unnamed: C40.2, U3.A12 (TX_EXT_LO_IN)
unnamed: C37.2, C56.2, U3.M12 (XTALN)
unnamed: R3.2, U4.8 (EN)
unnamed: R10.1, X1.1 (Tri-State)
P20-: J4.2, U1.P19 (IO_L13N_T2_MRCC_34)
PL_CLK: R21.2, U1.V13 (IO_L3N_T0_DQS_34)
PMIC_INT: RN12.2 (R2.1), U7.43 (INTn)
PMIC_PON: J5.17, U7.17 (PONKEYn)
PMIC_nRST: J2.1, RN12.1 (R1.1), U1.C7 (PS_POR_B_500), U7.1 (RSTn)
PROGRAM: RN9.8 (R1.2), U1.L6 (PROGRAM_B_0)
PS_CLK: R9.2, U1.E7 (PS_CLK_500)
PS_SRST: J2.6, RN10.4 (R4.1), U1.B10 (PS_SRST_B_501)
SD0_CK: J1.5 (CLK), R11.2
SD0_CMD: J1.3 (CMD), U1.C17 (PS_MIO41_501)
SD0_D0: J1.7 (DAT0), U1.E12 (PS_MIO42_501)
SD0_D1: J1.8 (DAT1), U1.A9 (PS_MIO43_501)
SD0_D2: J1.1 (DAT2), U1.F13 (PS_MIO44_501)
SD0_D3: J1.2 (DAT3/CD), U1.B15 (PS_MIO45_501)
T20+: J4.3, U1.P20 (IO_L14N_T2_SRCC_34)
TTY_MISO: J8.4, U4.30 (RXD0)
TTY_MOSI: J8.3, U4.31 (TXD0)
U18+: J4.21, U1.U18 (IO_L12P_T1_MRCC_34)
U20-: J4.4, U1.T20 (IO_L15P_T2_DQS_34)
USB_D+: J9.2, U4.18 (IO13)
USB_D-: J9.1, U4.17 (IO12)
V15+: J4.25, U1.V15 (IO_L10P_T1_34)
V16+: J4.23, U1.V16 (IO_L18P_T2_34)
V18: J4.20, U1.V18 (IO_L21N_T3_DQS_34)
V20+: J4.5, U1.T19 (IO_25_34)
VCC_DDR: C1.1, C2.1, C3.1, C4.1, C5.1, C6.1, C7.1, C8.1, C9.1, C10.1, C11.1, C12.1, C13.1, C14.1, C15.1, C16.1, C17.1, C19.1, C25.1, C27.1, C100.1, C101.1, L3.2, R4.2, U1.A3 (VCCO_DDR_502[10]), U1.D2 (VCCO_DDR_502[10]), U1.E5 (VCCO_DDR_502[10]), U1.G1 (VCCO_DDR_502[10]), U1.H4 (VCCO_DDR_502[10]), U1.L3 (VCCO_DDR_502[10]), U1.P2 (VCCO_DDR_502[10]), U1.R5 (VCCO_DDR_502[10]), U1.U1 (VCCO_DDR_502[10]), U1.V4 (VCCO_DDR_502[10]), U2.A1 (VDDQ), U2.A8 (VDDQ), U2.B2 (VDD), U2.C1 (VDDQ), U2.C9 (VDDQ), U2.D2 (VDDQ), U2.D9 (VDD), U2.E9 (VDDQ), U2.F1 (VDDQ), U2.G7 (VDD), U2.H2 (VDDQ), U2.H9 (VDDQ), U2.K2 (VDD), U2.K8 (VDD), U2.N1 (VDD), U2.N9 (VDD), U2.R1 (VDD), U2.R9 (VDD), U7.9 (VOUT2), U7.13 (LDO3IN)
VDD: C110.1, C122.1, C123.1, C124.1, C125.1, C126.1, J6.4, U1.N19 (VCCO_34[6]), U1.R15 (VCCO_34[6]), U1.T18 (VCCO_34[6]), U1.V14 (VCCO_34[6]), U1.W17 (VCCO_34[6]), U1.Y20 (VCCO_34[6]), U7.23 (LDO1OUT)
VREF_DDR: C103.1, U7.16 (VREFDDR)
VTT_DDR: C115.1, U7.14 (LDO3OUT)
W15-: J4.24, U1.W15 (IO_L10N_T1_34)
W16-: J4.22, U1.W16 (IO_L18N_T2_34)
W18+: J4.16, U1.W18 (IO_L22P_T3_34)
W19-: J4.14, U1.W19 (IO_L22N_T3_34)
W20-: J4.6, U1.U20 (IO_L15N_T2_DQS_34)
Y16: J4.18, U1.Y16 (IO_L7P_T1_34)
Y16+: J4.7, U1.U19 (IO_L12N_T1_MRCC_34)
Y17: J4.17, U1.Y17 (IO_L7N_T1_34)
Y17-: J4.8, U1.V20 (IO_L16P_T2_34)
Y18+: J4.15, U1.Y18 (IO_L17P_T2_34)
Y19-: J4.13, U1.Y19 (IO_L17N_T2_34)

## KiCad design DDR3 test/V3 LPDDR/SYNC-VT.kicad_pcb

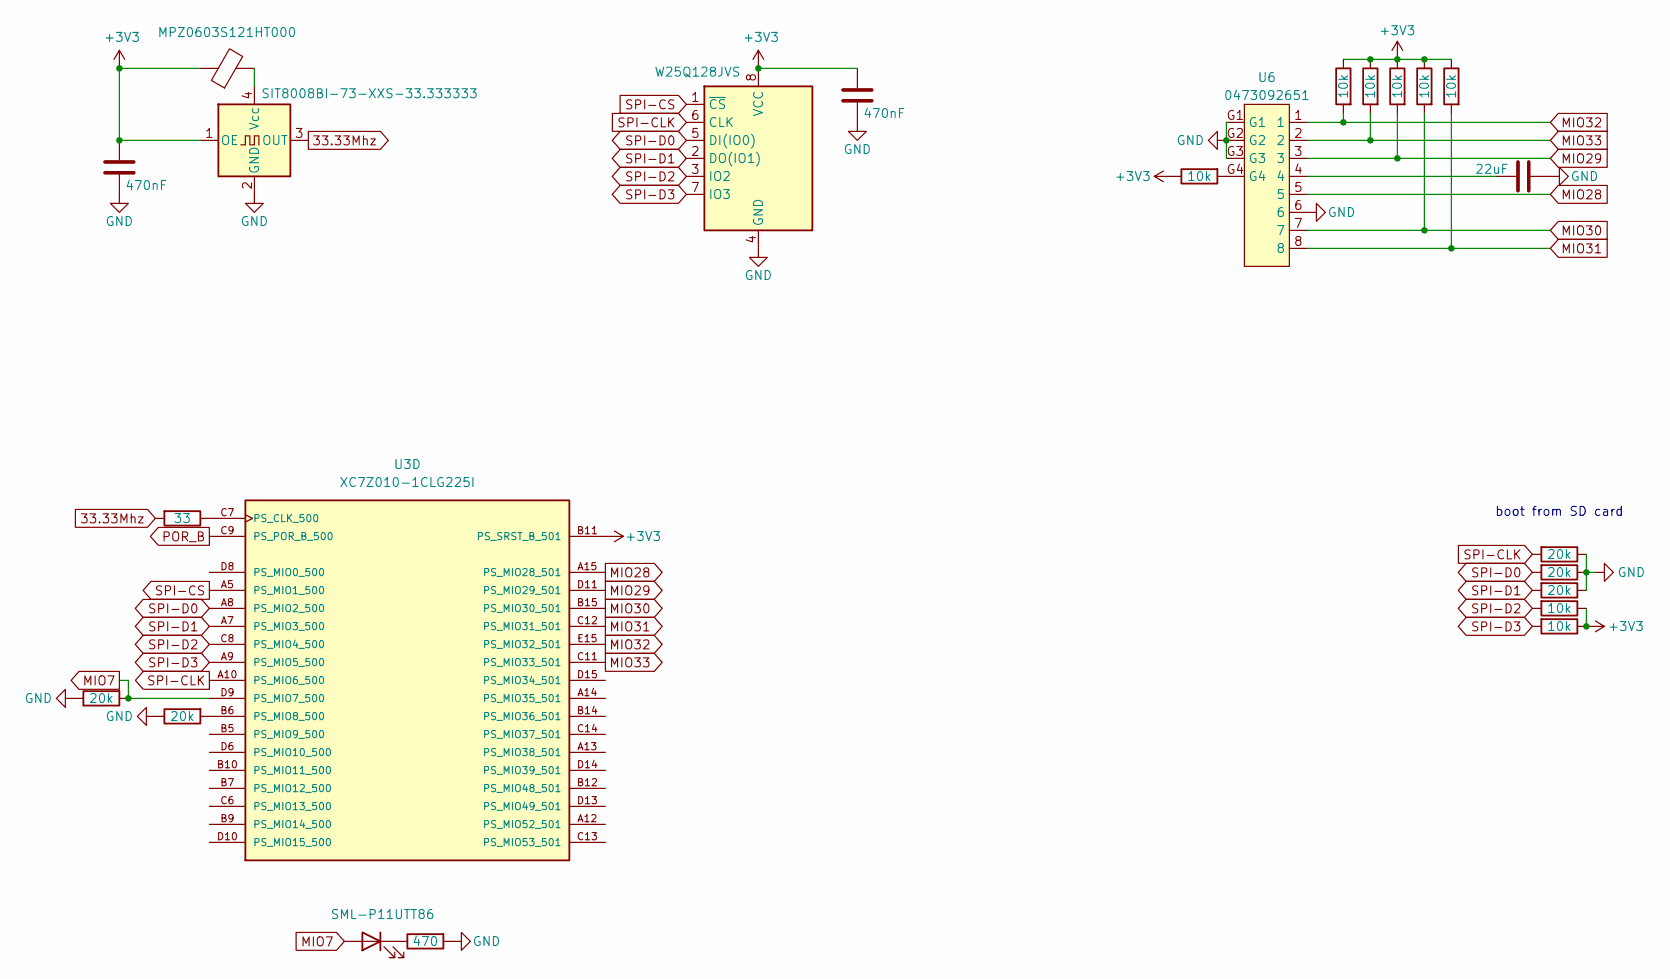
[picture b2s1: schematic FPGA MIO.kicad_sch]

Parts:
C1: 22uF; C_0402_1005Metric
C26, C27: 470nF; C_0201_0603Metric
D2: SML-P11UTT86; LED_0402_1005Metric
FB3: MPZ0603S121HT000; C_0201_0603Metric
R14, R15, R16, R17, R20: 20k; R_0201_0603Metric
R18, R19, R23, R24, R25, R26, R27, R28: 10k; R_0402_1005Metric
R21: 33; R_0201_0603Metric
R22: 470; R_0201_0603Metric
U3: XC7Z010-1CLG225I; BGA225C80P15X15_1300X1300X150N; MPN XC7Z010-1CLG225I
U5: W25Q128JVS; SOIC-8_5.23x5.23mm_P1.27mm
U6: 0473092651; CONN12_47309-2651_MOL
X1: SIT8008BI-73-XXS-33.333333; Oscillator_SMD_SeikoEpson_SG210-4Pin_2.5x2.0mm

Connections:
33.33Mhz: R21.2, X1.3 (OUT)
+3V3: C26.1, C27.1, FB3.1, R18.1, R19.1, R23.1, R24.1, R25.1, R26.1, R27.1, R28.1, U3.B11 (PS_SRST_B_501), U5.8 (VCC), X1.1 (OE); also elsewhere on the board
GND: C1.2, C26.2, C27.2, R14.1, R15.1, R16.1, R17.1, R20.1, R22.2, U5.4 (GND), U6.6, U6.G1, U6.G2, U6.G3, X1.2 (GND); also elsewhere on the board
MIO7: D2.2 (A), R20.2, U3.D9 (PS_MIO7_500)
MIO28: U3.A15 (PS_MIO28_501), U6.5
MIO29: R26.2, U3.D11 (PS_MIO29_501), U6.3
MIO30: R27.2, U3.B15 (PS_MIO30_501), U6.7
MIO31: R28.2, U3.C12 (PS_MIO31_501), U6.8
MIO32: R24.2, U3.E15 (PS_MIO32_501), U6.1
MIO33: R25.2, U3.C11 (PS_MIO33_501), U6.2
unnamed: C1.1, U6.4
unnamed: D2.1 (K), R22.1
unnamed: R23.2, U6.G4
unnamed: R21.1, U3.C7 (PS_CLK_500)
unnamed: R14.2, U3.B6 (PS_MIO8_500)
unnamed: FB3.2, X1.4 (Vcc)
POR_B: U3.C9 (PS_POR_B_500); also elsewhere on the board
SPI-CLK: R15.2, U3.A10 (PS_MIO6_500), U5.6 (CLK)
SPI-CS: U3.A5 (PS_MIO1_500), U5.1 (~CS)
SPI-D0: R16.2, U3.A8 (PS_MIO2_500), U5.5 (DI(IO0))
SPI-D1: R17.2, U3.A7 (PS_MIO3_500), U5.2 (DO(IO1))
SPI-D2: R18.2, U3.C8 (PS_MIO4_500), U5.3 (IO2)
SPI-D3: R19.2, U3.A9 (PS_MIO5_500), U5.7 (IO3)

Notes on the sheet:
boot from SD card

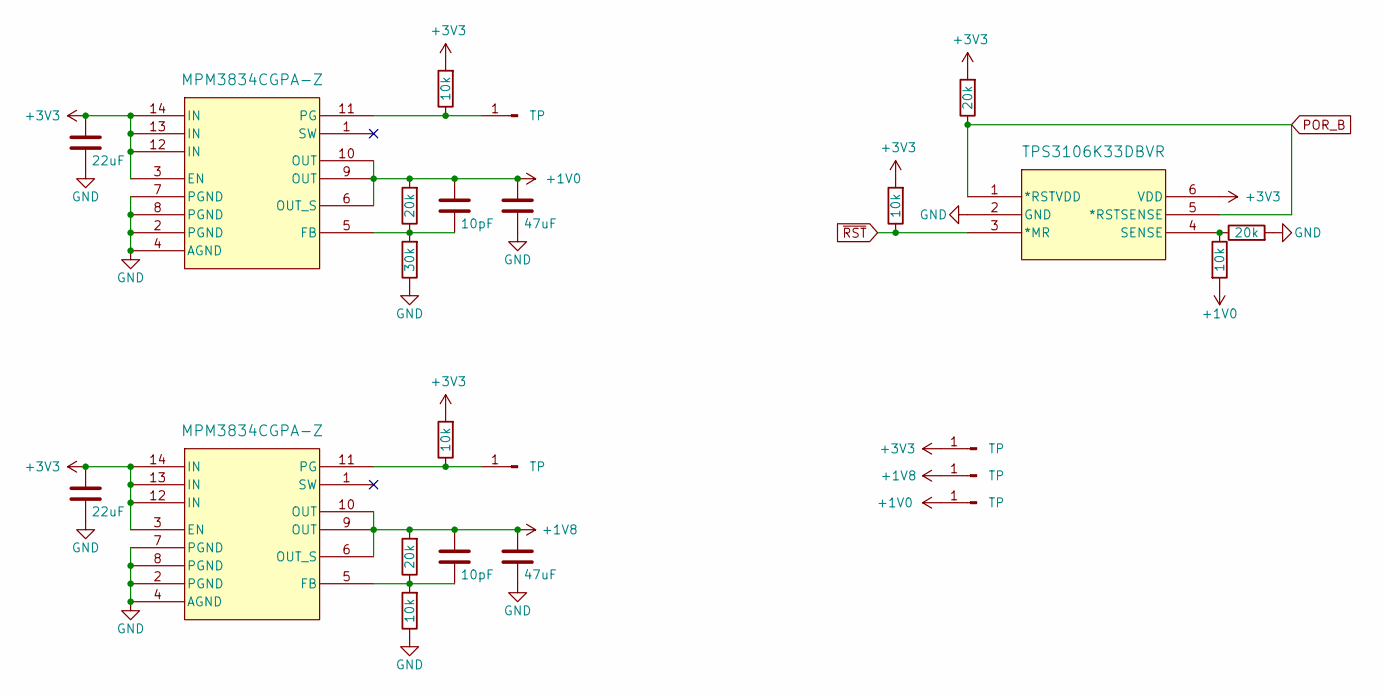
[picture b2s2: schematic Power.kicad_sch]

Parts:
C5, C11: 10pF; C_0201_0603Metric
C8, C10: 22uF; C_0402_1005Metric
C9, C12: 47uF; C_0805_2012Metric
R1, R3, R8, R10: 20k; C_0201_0603Metric
R2: 30k; C_0402_1005Metric
R4, R5, R6, R7, R9: 10k; C_0402_1005Metric
TP1, TP2, TP3, TP4, TP5: TP; TestPoint_Pad_1.0x1.0mm
U1, U2: MPM3834CGPA-Z; ECLGA-14_MPM3834C_MNP
U4: TPS3106K33DBVR; DBV6-L

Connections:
+1V0: C5.1, C9.1, R1.2, R9.2, TP5.1, U1.6 (OUT_S), U1.9 (OUT), U1.10 (OUT); also elsewhere on the board
+1V8: C11.1, C12.1, R3.2, TP4.1, U2.6 (OUT_S), U2.9 (OUT), U2.10 (OUT); also elsewhere on the board
+3V3: C8.1, C10.1, R4.2, R6.2, R7.2, R10.2, TP3.1, U1.3 (EN), U1.12 (IN), U1.13 (IN), U1.14 (IN), U2.3 (EN), U2.12 (IN), U2.13 (IN), U2.14 (IN), U4.6 (VDD); also elsewhere on the board
GND: C8.2, C9.2, C10.2, C12.2, R2.1, R5.1, R8.2, U1.2 (PGND), U1.4 (AGND), U1.7 (PGND), U1.8 (PGND), U2.2 (PGND), U2.4 (AGND), U2.7 (PGND), U2.8 (PGND), U4.2 (GND); also elsewhere on the board
unnamed: R6.1, TP1.1, U2.11 (PG)
unnamed: R4.1, TP2.1, U1.11 (PG)
unnamed: C5.2, R1.1, R2.2, U1.5 (FB)
unnamed: C11.2, R3.1, R5.2, U2.5 (FB)
unnamed: R8.1, R9.1, U4.4 (SENSE)
POR_B: R10.1, U4.1 (*RSTVDD), U4.5 (*RSTSENSE); also elsewhere on the board
~RST: R7.1, U4.3 (*MR)

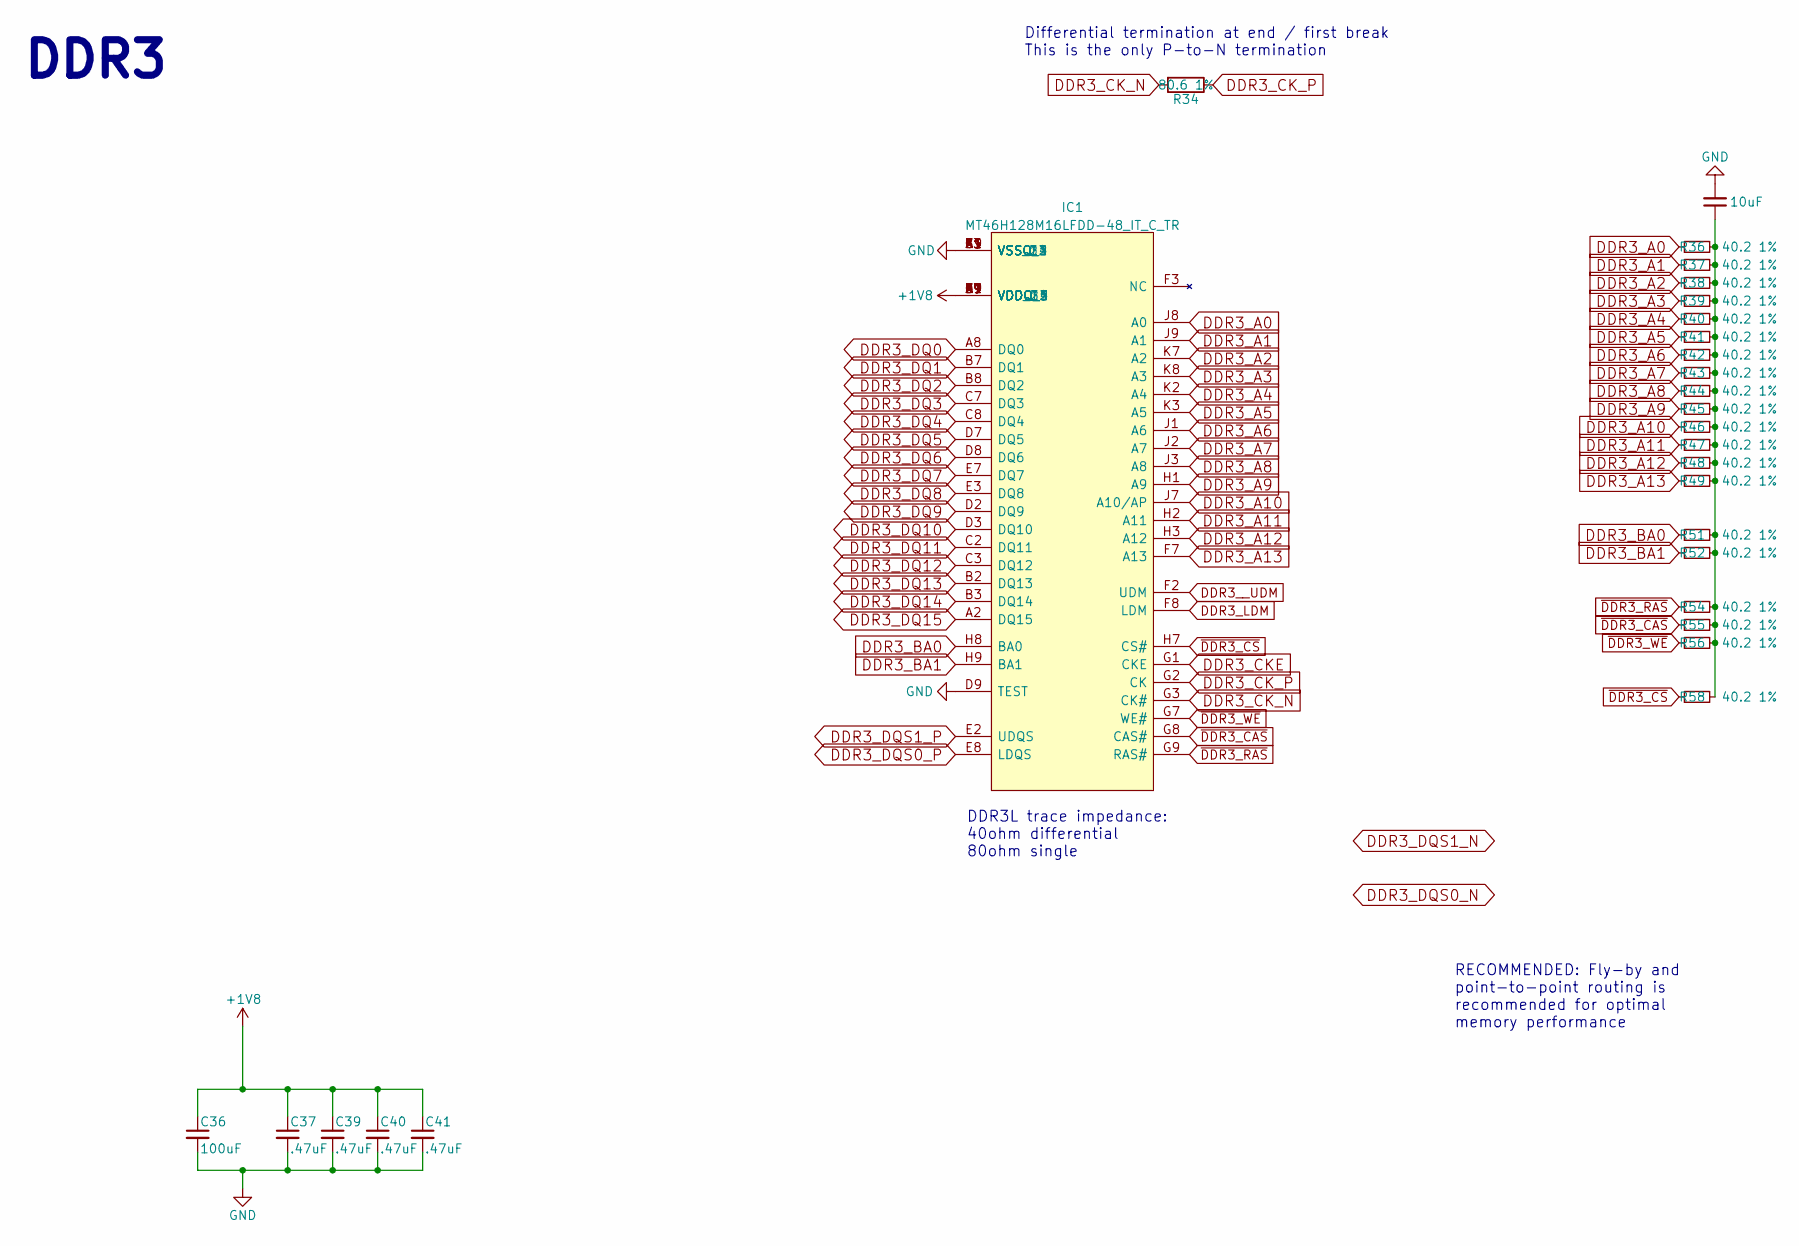
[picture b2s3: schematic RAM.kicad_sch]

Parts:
C36: 100uF; C_1206_3216Metric; MPN JMK325ABJ107MM-P
C37, C39, C40, C41: .47uF; C_1206_3216Metric; MPN CC0402KRX5R5BB474
C38: 10uF; C_0402_1005Metric
IC1: MT46H128M16LFDD-48_IT_C_TR; BGA60C80P9X10_800X900X100; Mouser Part Number 340-242388-REEL
R34: 80.6 1%; R_0603_1608Metric; MPN RC0402FR-0780R6L
R36, R37, R38, R39, R40, R41, R42, R43, R44, R45, R46, R47, R48, R49, R51, R52, R54, R55, R56, R58: 40.2 1%; R_0201_0603Metric; MPN RC0402FR-0740R2L

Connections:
+1V8: C36.1, C37.1, C39.1, C40.1, C41.1, IC1.A7 (VDDQ_1), IC1.A9 (VDD_1), IC1.B1 (VDDQ_2), IC1.C9 (VDDQ_3), IC1.D1 (VDDQ_4), IC1.E9 (VDDQ_5), IC1.F9 (VDD_2), IC1.K9 (VDD_3); also elsewhere on the board
DDR3_A0: IC1.J8 (A0), R36.1; also elsewhere on the board
DDR3_A1: IC1.J9 (A1), R37.1; also elsewhere on the board
DDR3_A2: IC1.K7 (A2), R38.1; also elsewhere on the board
DDR3_A3: IC1.K8 (A3), R39.1; also elsewhere on the board
DDR3_A4: IC1.K2 (A4), R40.1; also elsewhere on the board
DDR3_A5: IC1.K3 (A5), R41.1; also elsewhere on the board
DDR3_A6: IC1.J1 (A6), R42.1; also elsewhere on the board
DDR3_A7: IC1.J2 (A7), R43.1; also elsewhere on the board
DDR3_A8: IC1.J3 (A8), R44.1; also elsewhere on the board
DDR3_A9: IC1.H1 (A9), R45.1; also elsewhere on the board
DDR3_A10: IC1.J7 (A10/AP), R46.1; also elsewhere on the board
DDR3_A11: IC1.H2 (A11), R47.1; also elsewhere on the board
DDR3_A12: IC1.H3 (A12), R48.1; also elsewhere on the board
DDR3_A13: IC1.F7 (A13), R49.1; also elsewhere on the board
DDR3_BA0: IC1.H8 (BA0), R51.1; also elsewhere on the board
DDR3_BA1: IC1.H9 (BA1), R52.1; also elsewhere on the board
DDR3_CKE: IC1.G1 (CKE); also elsewhere on the board
DDR3_CK_N: IC1.G3 (CK#), R34.2; also elsewhere on the board
DDR3_CK_P: IC1.G2 (CK), R34.1; also elsewhere on the board
DDR3_DQ0: IC1.A8 (DQ0); also elsewhere on the board
DDR3_DQ1: IC1.B7 (DQ1); also elsewhere on the board
DDR3_DQ2: IC1.B8 (DQ2); also elsewhere on the board
DDR3_DQ3: IC1.C7 (DQ3); also elsewhere on the board
DDR3_DQ4: IC1.C8 (DQ4); also elsewhere on the board
DDR3_DQ5: IC1.D7 (DQ5); also elsewhere on the board
DDR3_DQ6: IC1.D8 (DQ6); also elsewhere on the board
DDR3_DQ7: IC1.E7 (DQ7); also elsewhere on the board
DDR3_DQ8: IC1.E3 (DQ8); also elsewhere on the board
DDR3_DQ9: IC1.D2 (DQ9); also elsewhere on the board
DDR3_DQ10: IC1.D3 (DQ10); also elsewhere on the board
DDR3_DQ11: IC1.C2 (DQ11); also elsewhere on the board
DDR3_DQ12: IC1.C3 (DQ12); also elsewhere on the board
DDR3_DQ13: IC1.B2 (DQ13); also elsewhere on the board
DDR3_DQ14: IC1.B3 (DQ14); also elsewhere on the board
DDR3_DQ15: IC1.A2 (DQ15); also elsewhere on the board
DDR3_DQS0_P: IC1.E8 (LDQS); also elsewhere on the board
DDR3_DQS1_P: IC1.E2 (UDQS); also elsewhere on the board
DDR3_LDM: IC1.F8 (LDM); also elsewhere on the board
DDR3__UDM: IC1.F2 (UDM); also elsewhere on the board
GND: C36.2, C37.2, C38.2, C39.2, C40.2, C41.2, IC1.A1 (VSS_1), IC1.A3 (VSSQ_1), IC1.B9 (VSSQ_2), IC1.C1 (VSSQ_3), IC1.D9 (TEST), IC1.E1 (VSSQ_4), IC1.F1 (VSS_2), IC1.K1 (VSS_3); also elsewhere on the board
unnamed: C38.1, R36.2, R37.2, R38.2, R39.2, R40.2, R41.2, R42.2, R43.2, R44.2, R45.2, R46.2, R47.2, R48.2, R49.2, R51.2, R52.2, R54.2, R55.2, R56.2, R58.2
~DDR3_CAS: IC1.G8 (CAS#), R55.1; also elsewhere on the board
~DDR3_CS: IC1.H7 (CS#), R58.1; also elsewhere on the board
~DDR3_RAS: IC1.G9 (RAS#), R54.1; also elsewhere on the board
~DDR3_WE: IC1.G7 (WE#), R56.1; also elsewhere on the board

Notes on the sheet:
DDR3
RECOMMENDED: Fly-by and point-to-point routing is recommended for optimal memory performance
DDR3L trace impedance: 40ohm differential 80ohm single
Differential termination at end / first break This is the only P-to-N termination

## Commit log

2024-05-25 Add KiCad
2024-06-05 New updates
    new notes and folders
2024-07-29 7/28 update
    Update various PCB and change the organization of the file
2024-08-02 8/1 update
2024-09-14 Hardware and Vivado change
    change to hardware
2024-12-27 12/26 update
    Prototype board added
2025-01-04 1/4 update
    update the breadboard version
2025-01-04 1/4 DDR3 test update
    add the ddr3 test file for kicad
2025-01-05 1/4 added library
2025-01-05 Added libraries to local project path and imported DDR3
2025-01-05 group ddr pins by function in symbol
    group ddr pins by function in symbol
2025-01-05 Resistor Footprints
    - Fixed resistor footprints
    - Re-added 3D models
    - Routed 1.5V reg
2025-01-18 BGA fanned out
2025-02-03 pin assignments
2025-03-09 added gitignore and removed autosave files
2025-03-17 3/16 update
2025-05-11 5/10 Changes
2025-05-31 5/31 update
